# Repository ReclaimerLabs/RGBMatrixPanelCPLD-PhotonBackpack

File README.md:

Copyright (c) 2016 Jason Cerundolo

Permission is hereby granted, free of charge, to any person obtaining a copy
of this software and associated documentation files (the "Software"), to deal
in the Software without restriction, including without limitation the rights
to use, copy, modify, merge, publish, distribute, sublicense, and/or sell
copies of the Software, and to permit persons to whom the Software is
furnished to do so, subject to the following conditions:

The above copyright notice and this permission notice shall be included in all
copies or substantial portions of the Software.

THE SOFTWARE IS PROVIDED "AS IS", WITHOUT WARRANTY OF ANY KIND, EXPRESS OR
IMPLIED, INCLUDING BUT NOT LIMITED TO THE WARRANTIES OF MERCHANTABILITY,
FITNESS FOR A PARTICULAR PURPOSE AND NONINFRINGEMENT. IN NO EVENT SHALL THE
AUTHORS OR COPYRIGHT HOLDERS BE LIABLE FOR ANY CLAIM, DAMAGES OR OTHER
LIABILITY, WHETHER IN AN ACTION OF CONTRACT, TORT OR OTHERWISE, ARISING FROM,
OUT OF OR IN CONNECTION WITH THE SOFTWARE OR THE USE OR OTHER DEALINGS IN THE
SOFTWARE.

RGB Matrix Panel CPLD Photon Backpack
==================

An interface board between a Particle Photon and an RGB Matrix Panel. 
A CPLD provides the interface between the two and handles protocol 
conversion. 

Pick up an RGB LED panel from Adafruit. 
https://www.adafruit.com/products/2026

Pick up a CPLD backpack from Reclaimer Labs. 
http://reclaimerlabs.com

Use with the matching Particle library. 
https://github.com/ReclaimerLabs/RGBmatrixpanelCPLD

This board allows the use of hardware timers and DMA to achieve low 
overhead transfers of information to the matrix panels. The CPLD on the 
backpack converts SPI data into the parallel format expected by 
the matrix panel. The only ongoing computation needed from the CPU 
is to set up the next DMA transfer and compute the time to display 
the next row of bit data. This take the CPU time needed from ~40% 
to <1% for two 32x32 panels. The limited factor is now RAM and 
transfer speed.

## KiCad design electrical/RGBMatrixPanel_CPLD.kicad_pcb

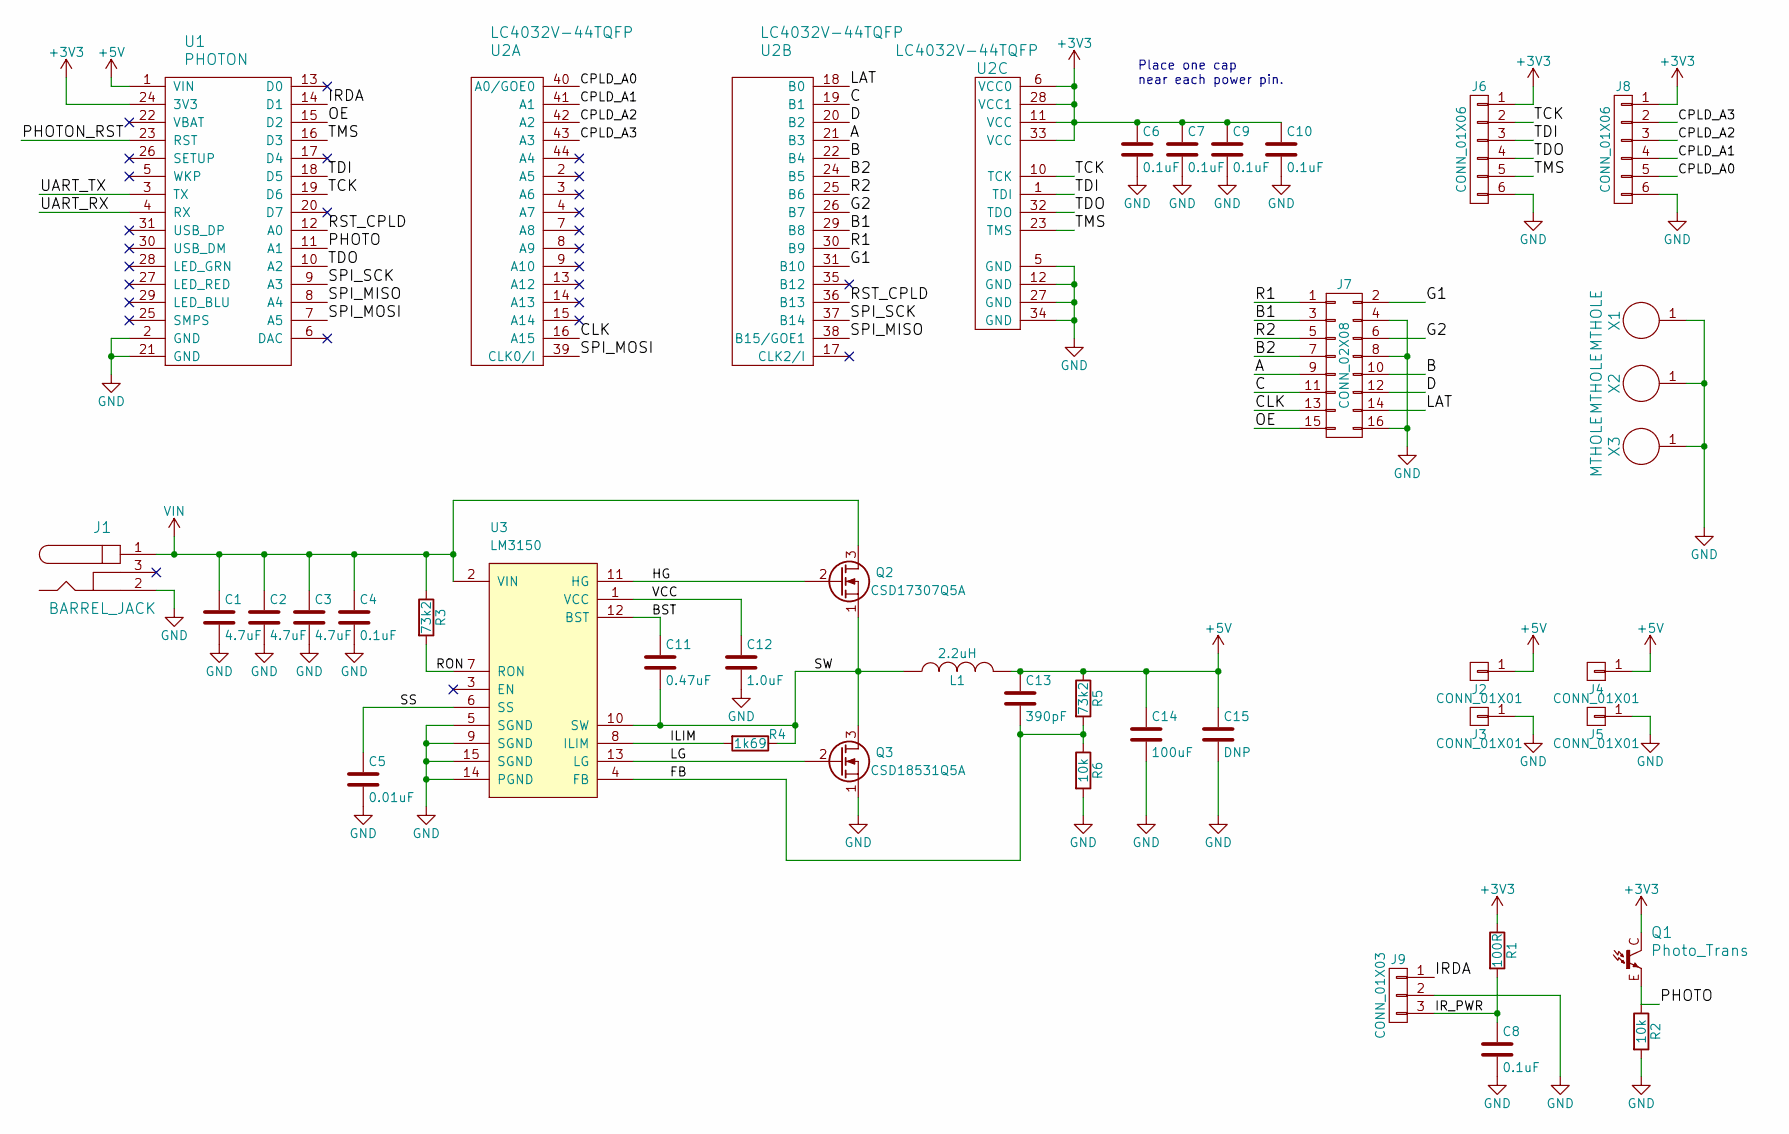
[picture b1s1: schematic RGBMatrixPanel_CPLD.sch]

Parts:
C1, C2, C3: 4.7uF; C_1206; Manufacturer Part Number GRM31CR71H475KA12L
C4: 0.1uF; C_0805; MacroFab Part Number MF-CAP-0805-0.1uF
C5: 0.01uF; C_0603; MacroFab Part Number MF-CAP-0603-0.01uF
C6, C7, C8: 0.1uF; C_0603; Manufacturer Part Number CC0603KRX7R7BB104
C9, C10: 0.1uF; C_0603; Manufacturer Part Number CC0603KRX7R9BB103
C11: 0.47uF; C_0805; Manufacturer Part Number EMK212B7474KD-T
C12: 1.0uF; C_0603; MacroFab Part Number MF-CAP-0603-1uF
C13: 390pF; C_0603; Manufacturer Part Number CL10B391KC8WPNC
C14: 100uF; C_1206; Manufacturer Part Number GRM31CR60J107ME39L
C15: DNP; C_1206; Manufacturer Part Number GRM31CR60J107ME39L
J1: BARREL_JACK; BARREL_JACK_PJ_202AH_Slots; Manufacturer Part Number PJ-202AH
J2, J3, J4, J5: CONN_01X01; 3547; Manufacturer Part Number 3547
J6, J8: CONN_01X06; Socket_Strip_Straight_1x06
J7: CONN_02X08; HEADER_THRU_02x08_POL; Manufacturer Part Number SFH11-PBPC-D08-ST-BK
J9: CONN_01X03; Socket_Strip_Straight_1x03
L1: 2.2uH; SRR1270; Manufacturer Part Number SRP1270-2R2M
Q1: Photo_Trans; Photo_Trans_0805; Manufacturer Part Number RPM-075PTT86
Q2: CSD17307Q5A; MOSFET_Q5A; Manufacturer Part Number CSD17307Q5A
Q3: CSD18531Q5A; MOSFET_Q5A; Manufacturer Part Number CSD18531Q5A
R1: 100R; C_0603; Manufacturer Part Number RC1608F101CS
R2: 10k; C_0603; Manufacturer Part Number RC1608F103CS
R3, R5: 73k2; C_0603; Manufacturer Part Number RC0603FR-0773K2L
R4: 1k69; C_0603; MacroFab Part Number MF-RES-0603-1.69K
R6: 10k; C_0603; MacroFab Part Number MF-RES-0603-10K
U1: PHOTON
U2: LC4032V-44TQFP; QFP_44; Manufacturer Part Number LC4032V-75TN44C
U3: LM3150; TSSOP-14-0.65mm-EP; Manufacturer Part Number LM3150MHX/NOPB
X1, X2, X3: MTHOLE; MountingHole_3.5mm_Pad_Via

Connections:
+3V3: C6.1, C7.1, C9.1, C10.1, J6.1, J8.1, Q1.C, R1.1, U1.24 (3V3), U2.6 (VCC0), U2.11 (VCC), U2.28 (VCC1), U2.33 (VCC)
+5V: C13.1, C14.1, C15.1, J2.1, J4.1, L1.2, R5.1, U1.1 (VIN)
/A: J7.9, U2.21 (B3)
/B: J7.10, U2.22 (B4)
/B1: J7.3, U2.29 (B8)
/B2: J7.7, U2.24 (B5)
/BST: C11.1, U3.12 (BST)
/C: J7.11, U2.19 (B1)
/CLK: J7.13, U2.16 (A15)
/CPLD_A0: J8.5, U2.40 (A0/GOE0)
/CPLD_A1: J8.4, U2.41 (A1)
/CPLD_A2: J8.3, U2.42 (A2)
/CPLD_A3: J8.2, U2.43 (A3)
/D: J7.12, U2.20 (B2)
/FB: C13.2, R5.2, R6.1, U3.4 (FB)
/G1: J7.2, U2.31 (B10)
/G2: J7.6, U2.26 (B7)
/HG: Q2.2 (G), U3.11 (HG)
/ILIM: R4.2, U3.8 (ILIM)
/IRDA: J9.1, U1.14 (D1)
/IR_PWR: C8.1, J9.3, R1.2
/LAT: J7.14, U2.18 (B0)
/LG: Q3.2 (G), U3.13 (LG)
/OE: J7.15, U1.15 (D2)
/PHOTO: Q1.E, R2.1, U1.11 (A1)
/PHOTON_RST: U1.23 (RST)
/R1: J7.1, U2.30 (B9)
/R2: J7.5, U2.25 (B6)
/RON: R3.2, U3.7 (RON)
/RST_CPLD: U1.12 (A0), U2.36 (B13)
/SPI_MISO: U1.8 (A4), U2.38 (B15/GOE1)
/SPI_MOSI: U1.7 (A5), U2.39 (CLK0/I)
/SPI_SCK: U1.9 (A3), U2.37 (B14)
/SS: C5.1, U3.6 (SS)
/SW: C11.2, L1.1, Q2.1 (S), Q3.3 (D), R4.1, U3.10 (SW)
/TCK: J6.2, U1.19 (D6), U2.10 (TCK)
/TDI: J6.3, U1.18 (D5), U2.1 (TDI)
/TDO: J6.4, U1.10 (A2), U2.32 (TDO)
/TMS: J6.5, U1.16 (D3), U2.23 (TMS)
/UART_RX: U1.4 (RX)
/UART_TX: U1.3 (TX)
/VCC: C12.1, U3.1 (VCC)
GND: C1.2, C2.2, C3.2, C4.2, C5.2, C6.2, C7.2, C8.2, C9.2, C10.2, C12.2, C14.2, C15.2, J1.2, J3.1, J5.1, J6.6, J7.4, J7.8, J7.16, J8.6, J9.2, Q3.1 (S), R2.2, R6.2, U1.2 (GND), U1.21 (GND), U2.5 (GND), U2.12 (GND), U2.27 (GND), U2.34 (GND), U3.5 (SGND), U3.9 (SGND), U3.14 (PGND), U3.15 (SGND), X1.1, X2.1, X3.1
VIN: C1.1, C2.1, C3.1, C4.1, J1.1, Q2.3 (D), R3.1, U3.2 (VIN)

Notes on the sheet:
Place one cap near each power pin.

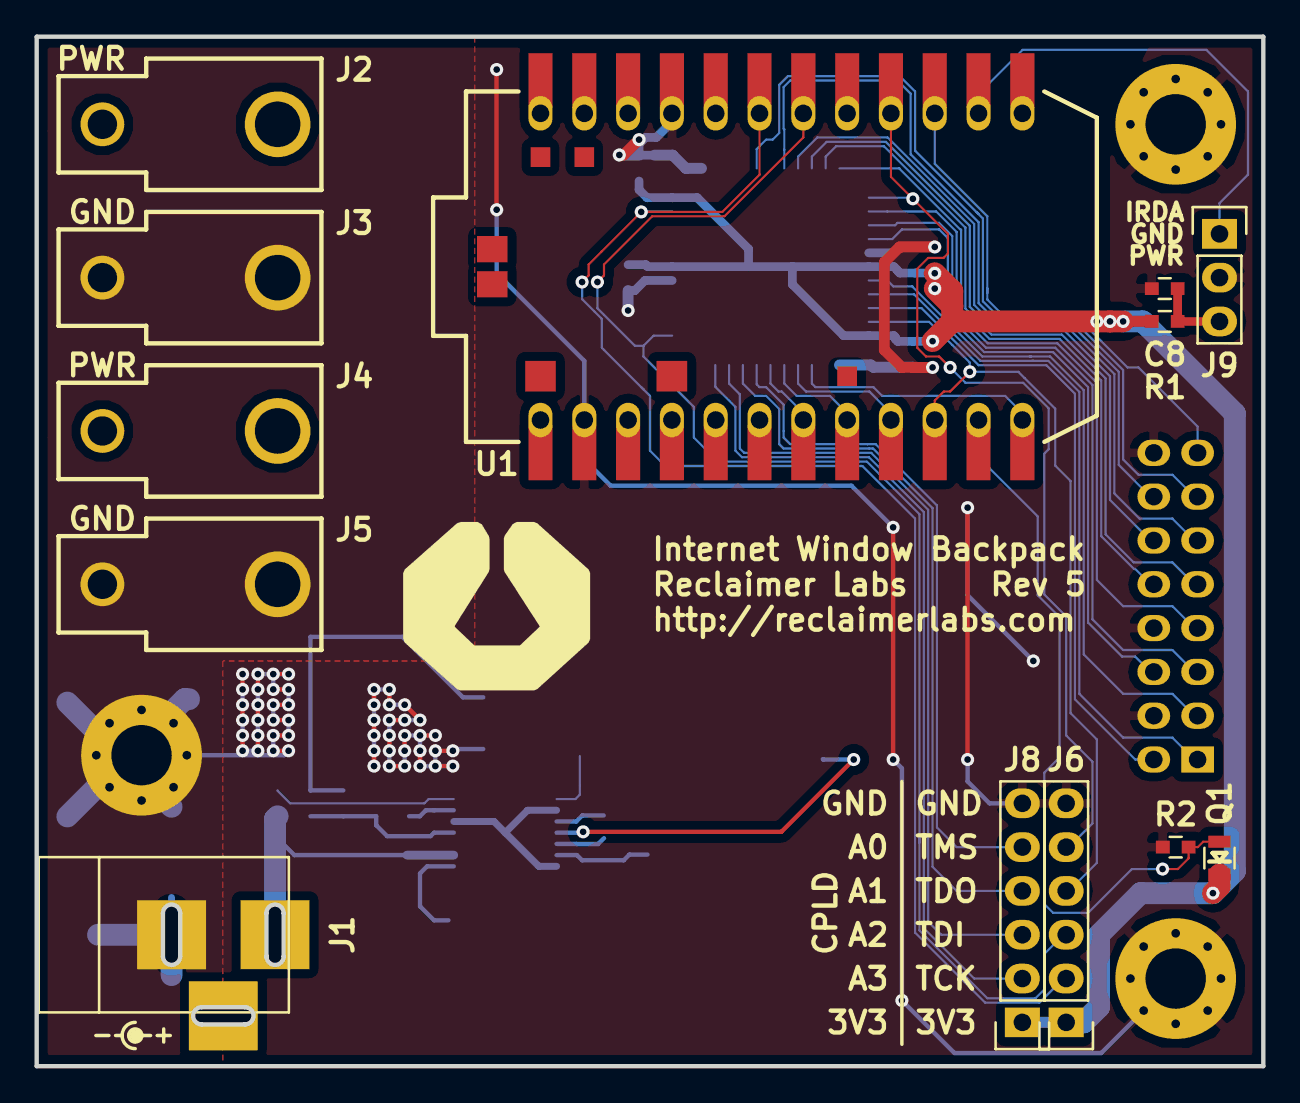
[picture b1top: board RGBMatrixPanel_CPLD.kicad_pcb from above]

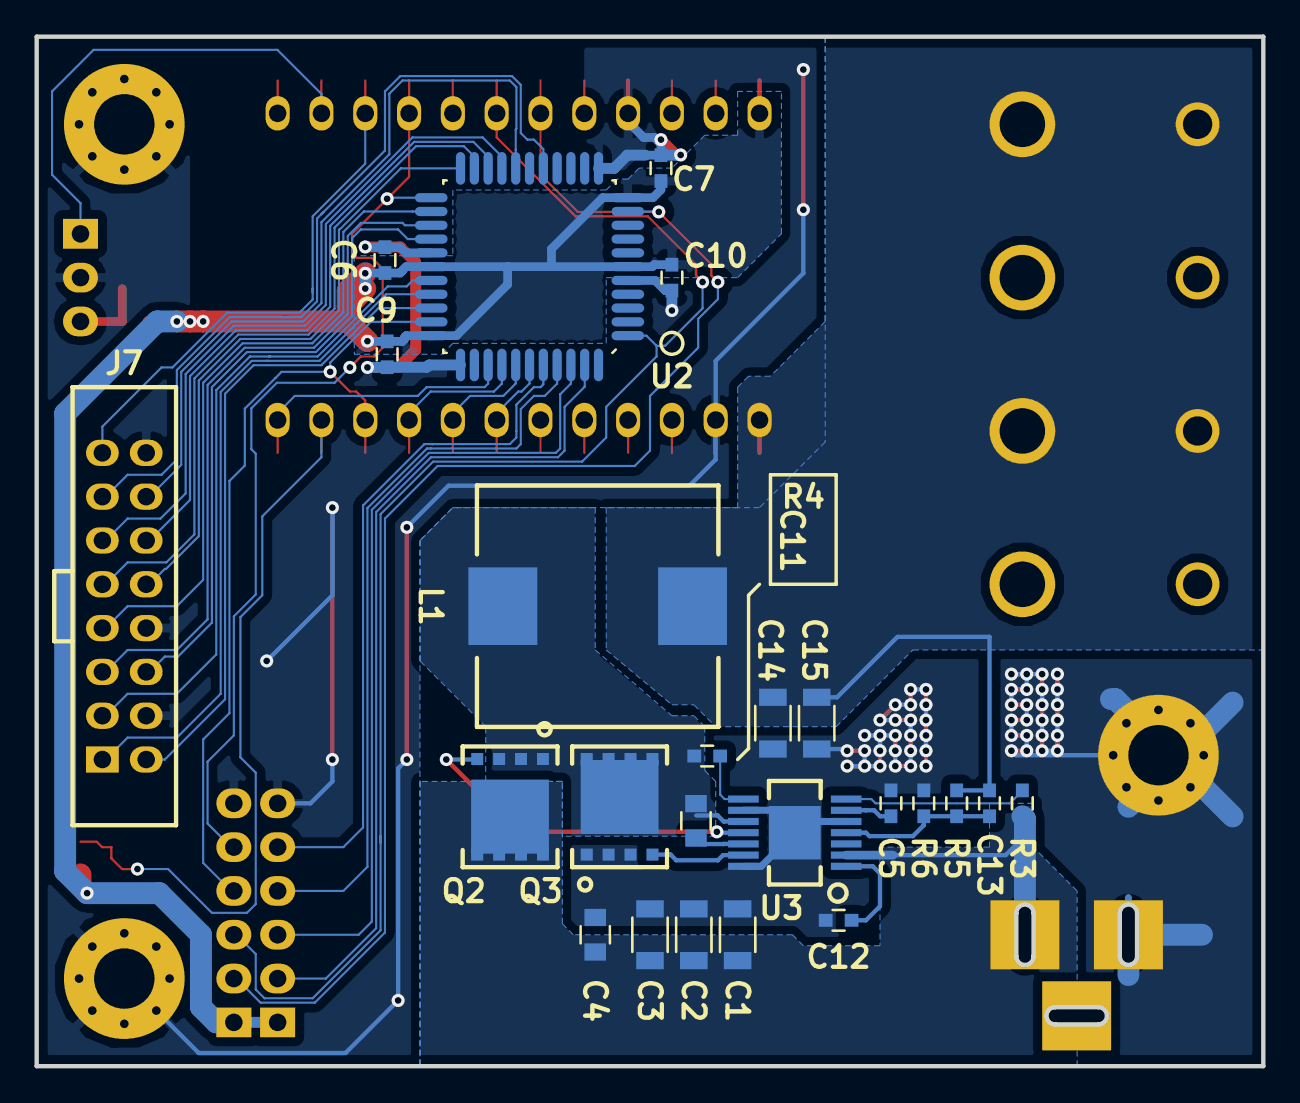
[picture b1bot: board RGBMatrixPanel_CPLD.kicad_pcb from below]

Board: 2 copper layers, 71.1 x 59.7 mm, 40 parts (24 on the bottom side), 41 nets.

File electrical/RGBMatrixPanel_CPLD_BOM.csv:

Reference, Value, Footprint, Datasheet, DNP, Manufacturer, Manufacturer Part Number, Supplier 1, Supplier 1 Part Number, MacroFab Part Number
U1,PHOTON,Reclaimer_Labs:PHOTON,,DNP,,,,,
U2,LC4032V-44TQFP,Reclaimer_Labs:QFP_44,,,Lattice,LC4032V-75TN44C,Digikey,220-1034-ND,
J7,CONN_02X08,Reclaimer_Labs:HEADER_THRU_02x08_POL,,,Sullins,SFH11-PBPC-D08-ST-BK,Digikey,S9196-ND,
C9,0.1uF,Capacitors_SMD:C_0603,,,Yageo,CC0603KRX7R9BB103,Digikey,311-1085-1-ND,
R2,10k,Capacitors_SMD:C_0603,,,Samsung,RC1608F103CS,Digikey,1276-3485-1-ND,
C8,0.1uF,Capacitors_SMD:C_0603,,,Yageo,CC0603KRX7R7BB104,Digikey,311-1088-1-ND,
R1,100R,Capacitors_SMD:C_0603,,,Samsung,RC1608F101CS,Digikey,1276-3482-1-ND,
J1,BARREL_JACK,Reclaimer_Labs:BARREL_JACK_PJ_202AH_Slots,,,CUI,PJ-202AH,Digikey,CP-202AH-ND,
Q1,Photo_Trans,Reclaimer_Labs:Photo_Trans_0805,,,Rohm,RPM-075PTT86,Digikey,511-1356-1-ND,
C6,0.1uF,Capacitors_SMD:C_0603,,,Yageo,CC0603KRX7R7BB104,Digikey,311-1088-1-ND,
C7,0.1uF,Capacitors_SMD:C_0603,,,Yageo,CC0603KRX7R7BB104,Digikey,311-1088-1-ND,
C10,0.1uF,Capacitors_SMD:C_0603,,,Yageo,CC0603KRX7R9BB103,Digikey,311-1085-1-ND,
X3,MTHOLE,Reclaimer_Labs:MountingHole_3.5mm_Pad_Via,
X1,MTHOLE,Reclaimer_Labs:MountingHole_3.5mm_Pad_Via,
X2,MTHOLE,Reclaimer_Labs:MountingHole_3.5mm_Pad_Via,
J2,CONN_01X01,Reclaimer_Labs:3547,,,Keystone,3547,Digikey,36-3547-ND,
J3,CONN_01X01,Reclaimer_Labs:3547,,,Keystone,3547,Digikey,36-3547-ND,
J4,CONN_01X01,Reclaimer_Labs:3547,,,Keystone,3547,Digikey,36-3547-ND,
J5,CONN_01X01,Reclaimer_Labs:3547,,,Keystone,3547,Digikey,36-3547-ND,
J8,CONN_01X06,Socket_Strips:Socket_Strip_Straight_1x06,
J6,CONN_01X06,Socket_Strips:Socket_Strip_Straight_1x06,
J9,CONN_01X03,Socket_Strips:Socket_Strip_Straight_1x03,
R3,73k2,Capacitors_SMD:C_0603,,,Yageo,RC0603FR-0773K2L,,,
C4,0.1uF,Capacitors_SMD:C_0805,,,,,,,MF-CAP-0805-0.1uF
C1,4.7uF,Capacitors_SMD:C_1206,,,Murata,GRM31CR71H475KA12L,,,
C5,0.01uF,Capacitors_SMD:C_0603,,,,,,,MF-CAP-0603-0.01uF
C11,0.47uF,Capacitors_SMD:C_0805,,,Taiyo,EMK212B7474KD-T,,,
C12,1.0uF,Capacitors_SMD:C_0603,,,,,,,MF-CAP-0603-1uF
U3,LM3150,Reclaimer_Labs:TSSOP-14-0.65mm-EP,,,TI,LM3150MHX/NOPB,,,
R6,10k,Capacitors_SMD:C_0603,,,,,,,MF-RES-0603-10K
L1,2.2uH,Reclaimer_Labs:SRR1270,,,Bourns,SRP1270-2R2M,,,
C13,390pF,Capacitors_SMD:C_0603,,,Samsung,CL10B391KC8WPNC,,,
R4,1k69,Capacitors_SMD:C_0603,,,,,,,MF-RES-0603-1.69K
C14,100uF,Capacitors_SMD:C_1206,,,Murata,GRM31CR60J107ME39L,,,
R5,73k2,Capacitors_SMD:C_0603,,,Yageo,RC0603FR-0773K2L,,,
C2,4.7uF,Capacitors_SMD:C_1206,,,Murata,GRM31CR71H475KA12L,,,
C3,4.7uF,Capacitors_SMD:C_1206,,,Murata,GRM31CR71H475KA12L,,,
C15,DNP,Capacitors_SMD:C_1206,,,Murata,GRM31CR60J107ME39L,,,
Q3,CSD18531Q5A,Reclaimer_Labs:MOSFET_Q5A,,,TI,CSD18531Q5A,,,
Q2,CSD17307Q5A,Reclaimer_Labs:MOSFET_Q5A,,,TI,CSD17307Q5A,,,

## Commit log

2016-05-01 :lollipop: Added .gitattributes & .gitignore files
2016-05-01 Initial Check-in
    Initial check-in of Rev 1 hardware.
2016-05-14 Debugging CPLD code
    Added timing diagrams for CPLD and low-level FW functions. Updated CPLD
    code to set a known reset state for latch_needed.
2016-05-16 Simplified CPLD code
    Removed row_inc_needed register to simply verilog code. Also updated
    timing diagrams to match new hardware code.
2016-06-14 Updating documentation for Rev 1
    Updating documentation, zipped up gerbers, and created c files for
    programming CPLD from Photon
2016-08-02 Rev 2
    Updated board to Rev 2. Removed buzzer. Reduced number spare GPIOs.
    Added HW to program CPLD from Photon. Updated CPLD pinout in Lattice SW.
2016-10-19 Rev 3
    Updates include new board outline to accomendate mounting to sheet metal
    frame
2016-12-24 moved mounting hole
    Moved mounting hole to better align with the sheet metal frame
2016-12-24 updated git ignore
    removing temp files from source control
2017-02-14 Rev 5
2017-05-30 Added buck converter
    Added an on-board 24V to 5V buck converter to lower the current going
    through the connector to a safe level. Now the magic smoke stays safely
    contained.
